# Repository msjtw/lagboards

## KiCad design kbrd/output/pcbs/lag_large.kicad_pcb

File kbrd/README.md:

```bash
ergogen . && flatpak --command=pcbnew run org.kicad.KiCad output/pcbs/lag_large.kicad_pcb                                                                                   
```

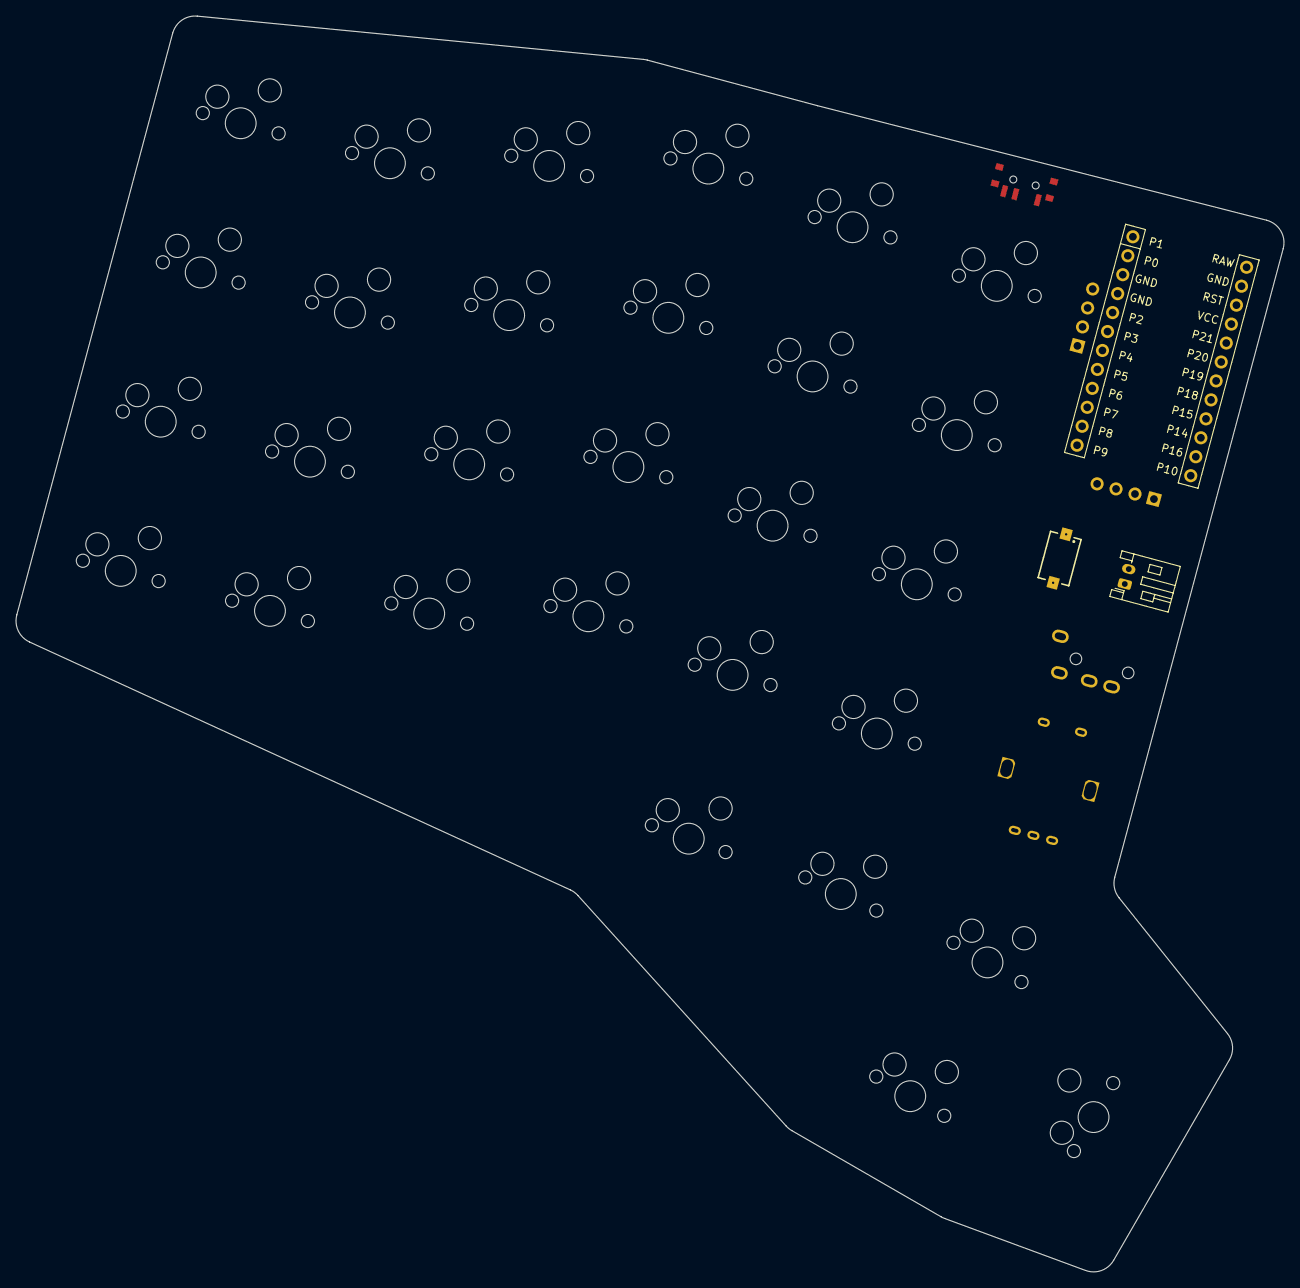
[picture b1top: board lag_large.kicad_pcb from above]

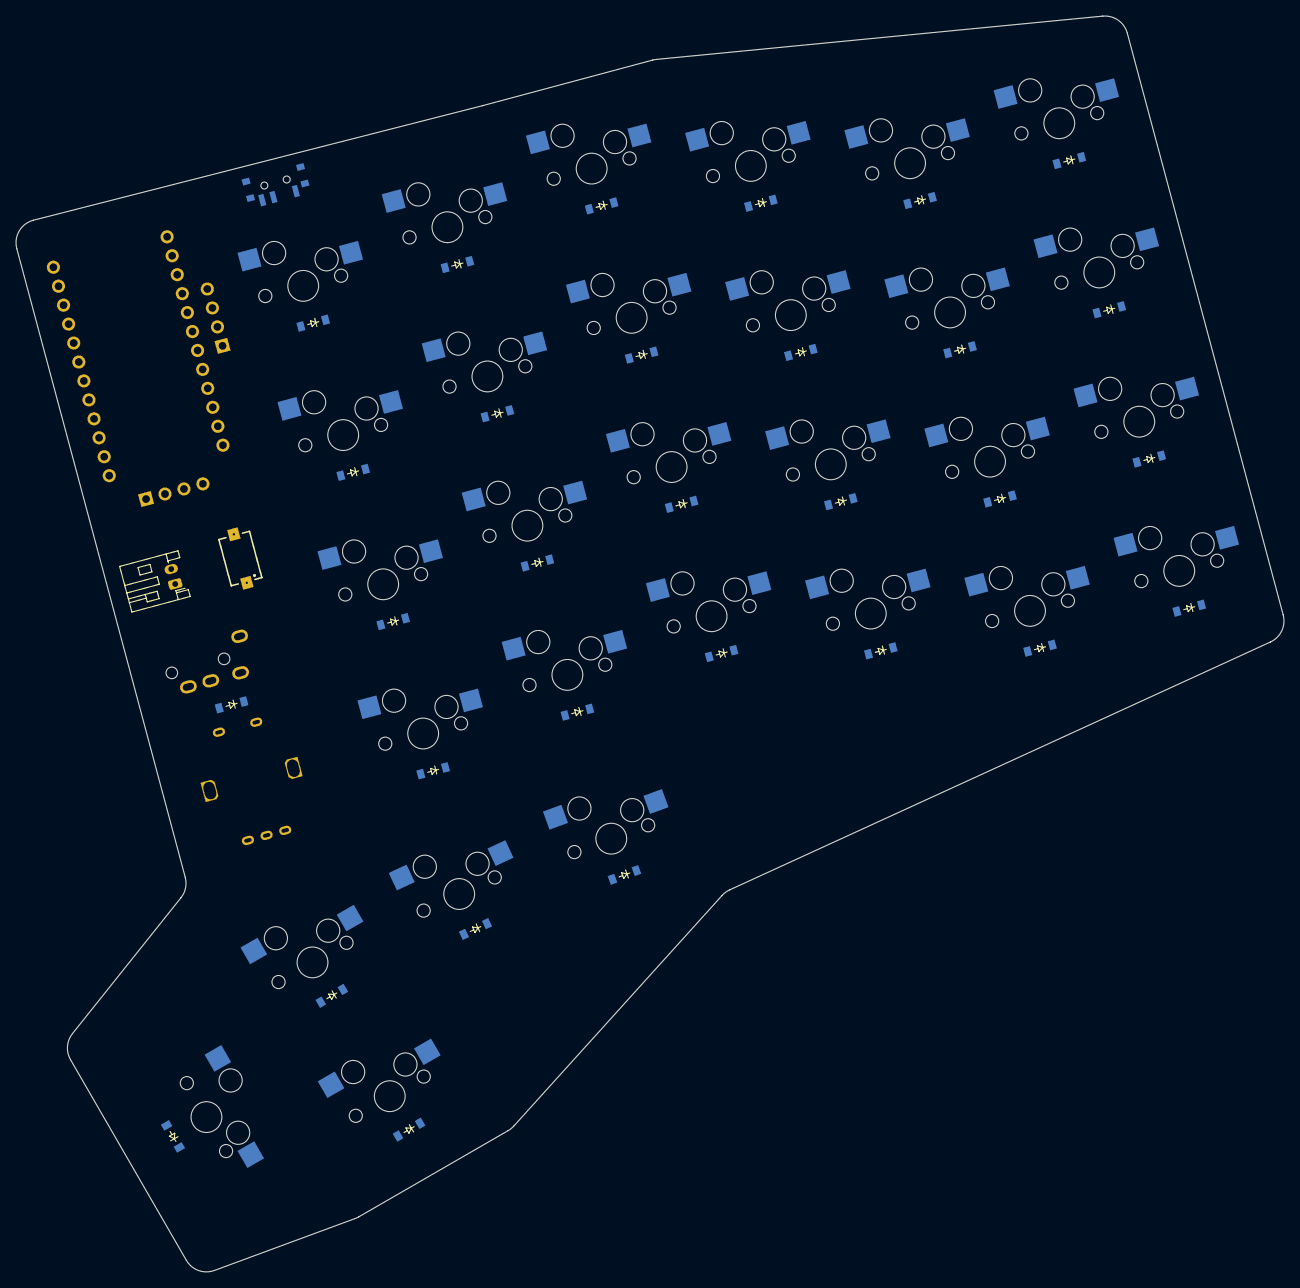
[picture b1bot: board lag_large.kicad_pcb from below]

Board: 2 copper layers, 164.2 x 162.6 mm, 67 parts (30 on the bottom side), 49 nets, no tracks yet.

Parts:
D1, D2, D3, D4, D5, D6, D7, D8, D9, D10, D11, D12, D13, D14, D15, D16, D17, D18, D19, D20, D21, D22, D23, D24, D25, D26, D27, D28, D29, D30: diode_tht_sod123
MCU1: mcu_supermini_nrf52840
OLED1, OLED2: OLED; OLED_headers
RE1: rotary_encoder_ec11_ec12
S1, S2, S3, S4, S5, S6, S7, S8, S9, S10, S11, S12, S13, S14, S15, S16, S17, S18, S19, S20, S21, S22, S23, S24, S25, S26, S27, S28, S29: MX
S30: 434121025816
T1: SW_SPDT_PCM12
TRRS1: trrs_pj320a
_1: JST_PH_S2B-PH-K_1x02_P2.00mm_Horizontal

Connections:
GND: MCU1.2, MCU1.21, MCU1.22, OLED1.1, OLED2.1, RE1.B, S30.2, TRRS1.2, _1.1
P1: MCU1.24, TRRS1.5
P2: MCU1.20, OLED1.4, OLED2.4
P3: MCU1.19, OLED1.3, OLED2.3
P4: MCU1.18, S1.1, S2.1, S3.1, S4.1, S25.1
P5: MCU1.17, S5.1, S6.1, S7.1, S8.1, S26.1
P6: MCU1.16, S9.1, S10.1, S11.1, S12.1, S28.1
P7: MCU1.15, S13.1, S14.1, S15.1, S16.1, S27.1
P8: MCU1.14, S17.1, S18.1, S19.1, S20.1, S29.1
P9: MCU1.13, RE1.S1, S21.1, S22.1, S23.1, S24.1
P10: D25.1, D26.1, D27.1, D28.1, D29.1, D30.1, MCU1.12
P14: D2.1, D6.1, D10.1, D14.1, D18.1, D22.1, MCU1.10
P15: D3.1, D7.1, D11.1, D15.1, D19.1, D23.1, MCU1.9
P16: D1.1, D5.1, D9.1, D13.1, D17.1, D21.1, MCU1.11
P18: D4.1, D8.1, D12.1, D16.1, D20.1, D24.1, MCU1.8
RAW: MCU1.1, T1.2
RST: MCU1.3, S30.1
VCC: MCU1.4, OLED1.2, OLED2.2, TRRS1.4
en_s2: D30.2, RE1.S2
index_bottom: D17.2, S17.2
index_home: D18.2, S18.2
index_num: D20.2, S20.2
index_top: D19.2, S19.2
inner_bottom: D21.2, S21.2
inner_home: D22.2, S22.2
inner_num: D24.2, S24.2
inner_rowb: D29.2, S29.2
inner_rowt: D27.2, S27.2
inner_top: D23.2, S23.2
middle_bottom: D13.2, S13.2
middle_home: D14.2, S14.2
middle_num: D16.2, S16.2
middle_rowb: D28.2, S28.2
middle_rowt: D26.2, S26.2
middle_top: D15.2, S15.2
outer_bottom: D1.2, S1.2
outer_home: D2.2, S2.2
outer_num: D4.2, S4.2
outer_rowt: D25.2, S25.2
outer_top: D3.2, S3.2
pinky_bottom: D5.2, S5.2
pinky_home: D6.2, S6.2
pinky_num: D8.2, S8.2
pinky_top: D7.2, S7.2
ring_bottom: D9.2, S9.2
ring_home: D10.2, S10.2
ring_num: D12.2, S12.2
ring_top: D11.2, S11.2
sw1: T1.1, _1.2

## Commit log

2025-08-19 init ErgoFunctor
2025-09-04 large keyboard
2025-09-04 pinout description
